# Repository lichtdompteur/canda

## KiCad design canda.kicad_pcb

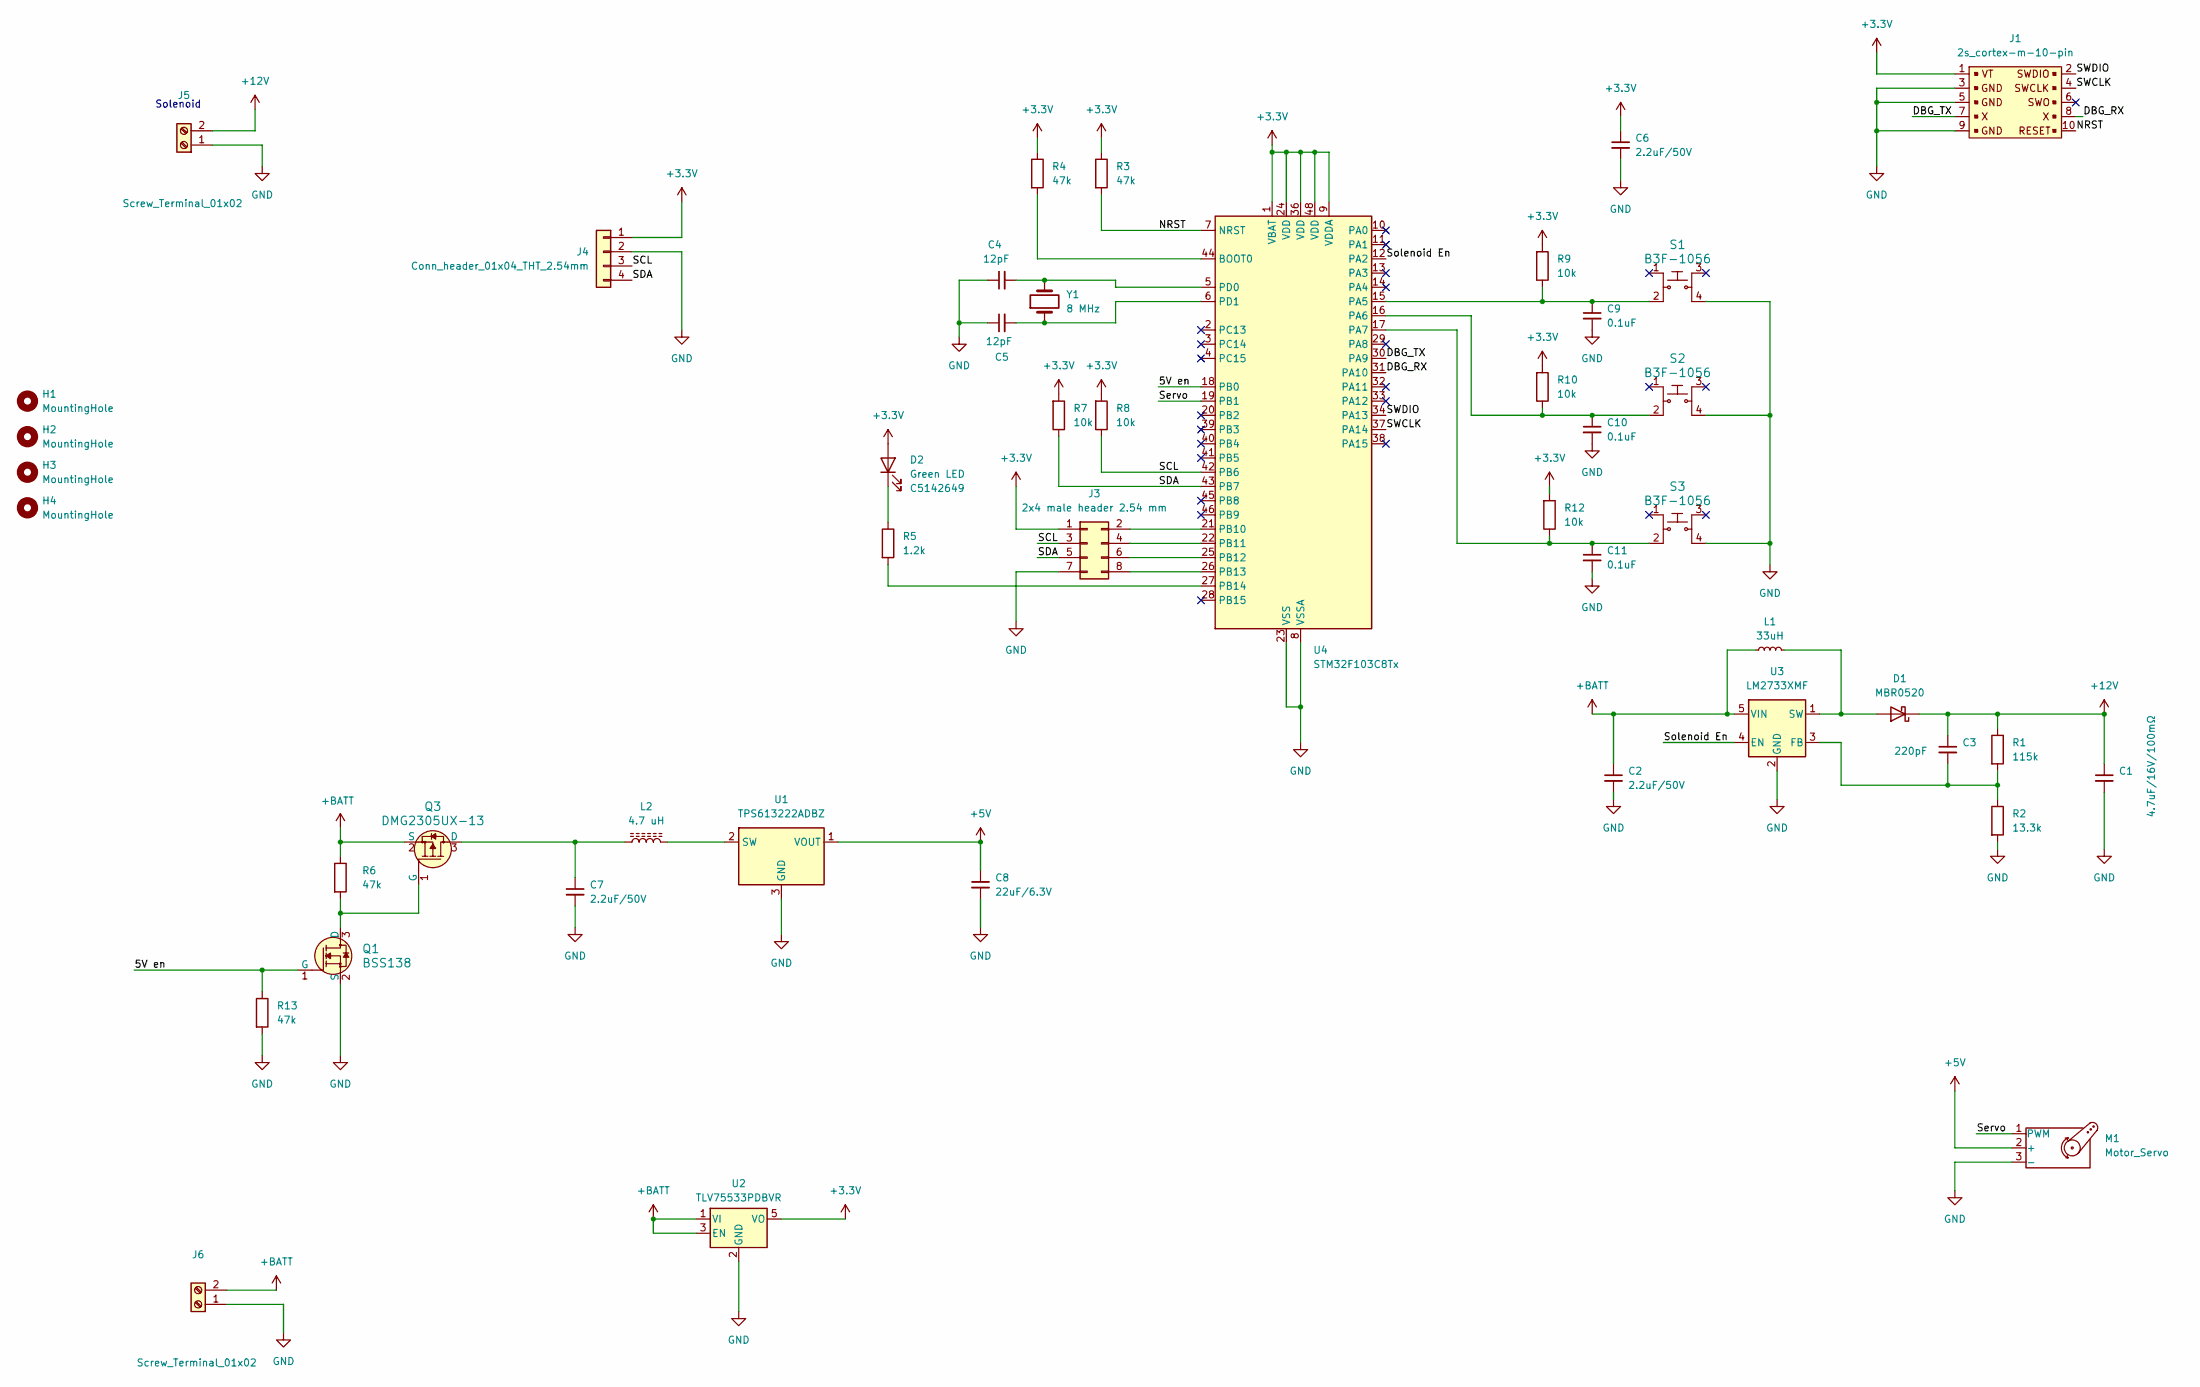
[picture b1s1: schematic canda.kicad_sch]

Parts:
C1: 4.7uF_1206_lowESR; C_1206_3216Metric; MPN EMF316AB7475KLHT; JLCPCB ID C2174986
C2, C6, C7: 2.2uF_1206_25V; C_1206_3216Metric; MPN CL31B225KBHNNNE; JLCPCB ID C12891
C3: 220pF_0603_25V; C_0603_1608Metric; MPN CC0603JRNPO9BN221; JLCPCB ID C1603
C4, C5: 12pF_0603_50V; C_0603_1608Metric; MPN C0603C120J5GACTU; JLCPCB ID C2168573
C8: 22uF_0805_6.3V; C_0805_2012Metric; MPN JMK212ABJ226MD-T; JLCPCB ID C45783
C9, C10, C11: 100nF_0603_16V; C_0603_1608Metric; MPN 0603YC104KAT2A; JLCPCB ID C14663
D1: MBR0520; D_SOD-123; MPN MBR0520-TP; Digi-Key_PN MBR0520TPMSTR-ND
D2: Green LED; LED_1206_3216Metric; MPN 150120GS75000; Digi-Key_PN 732-4990-1-ND
H1, H2, H3, H4: MountingHole; MountingHole_3.2mm_M3_ISO7380
J1: 2s_cortex-m-10-pin; PinHeader_2x5_P1.27_SMD; MPN FTSH-105-01-F-DV-K; Digi-Key_PN SAM8796-ND
J3: 2x4 male header 2.54 mm; PinHeader_2x04_P2.54mm_Vertical_SMD; MPN 54202-G0804LF; Digi-Key_PN 609-54202-G0804LF-ND
J4: Conn_header_01x04_THT_2.54mm; PinHeader_1x04_P2.54mm_Vertical; MPN 61300411121; Digi-Key_PN 732-5317-ND
J5, J6: Screw_Terminal_01x02; TerminalBlock_MaiXu_MX126-5.0-02P_1x02_P5.00mm; MPN 282836-2; Digi-Key_PN A98076-ND
L1: 33uH; L_Taiyo-Yuden_NR-60xx; MPN NR6028T330M; Digi-Key_PN 587-2631-2-ND
L2: 4.7 uH; L_Bourns-SRN6028; MPN NRS6028T4R7MMGKV; Digi-Key_PN 587-3639-2-ND
M1: Motor_Servo; PinHeader_1x03_P2.54mm_Vertical
Q1: BSS138; SOT-23-3; MPN BSS138; Digi-Key_PN BSS138CT-ND
Q3: DMG2305UX-13; SOT-23-3; MPN DMG2305UX-13; Digi-Key_PN DMG2305UX-13DICT-ND
R1: 115k_0805; R_0805_2012Metric; MPN RC0805FR-07115KL; JLCPCB ID C274364
R2: 13.3k_0805; R_0805_2012Metric; MPN RC0805FR-0713K3L; JLCPCB ID C274912
R3, R4, R6, R13: 47k_0805; R_0805_2012Metric; MPN RC0805FR-0747KL; JLCPCB ID C126351
R5: 1.2k_0805; R_0805_2012Metric; MPN RC0805FR-071K2L; JLCPCB ID C114526
R7, R8, R9, R10, R12: 10k_0805; R_0805_2012Metric; MPN CRCW080510K0FKEA; JLCPCB ID C84376
S1, S2, S3: B3F-1056; SW_TH_Tactile_Omron_B3F-1052; MPN B3F-1056; Digi-Key_PN Z4425-ND
U1: TPS613222ADBZ; SOT-23
U2: TLV75533PDBVR; SOT-23-5; MPN TLV75533PDBVR; Digi-Key_PN 296-50411-1-ND
U3: LM2733XMF; SOT-23-5; MPN LM2733XMF/NOPB; Digi-Key_PN LM2733XMF/NOPBTR-ND
U4: STM32F103C8Tx; LQFP-48_7x7mm_P0.5mm
Y1: 8 MHz; Crystal_HC49-U_Vertical; MPN ATS08A-E

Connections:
+3.3V: C6.1, D2.2 (A), J1.1, J3.1, J4.1, R3.1, R4.1, R7.1, R8.1, R9.1, R10.1, R12.1, U2.5 (VO), U4.1 (VBAT), U4.9 (VDDA), U4.24 (VDD), U4.36 (VDD), U4.48 (VDD)
+5V: C8.1, M1.2 (+), U1.1 (VOUT)
+12V: C1.1, C3.1, D1.1 (K), J5.2, R1.1
+BATT: C2.1, J6.2, L1.1, Q3.2 (S), R6.1, U2.1 (VI), U2.3 (EN), U3.5 (VIN)
/5V en: Q1.1 (G), R13.1, U4.18 (PB0)
/DBG_RX: J1.8, U4.31 (PA10)
/DBG_TX: J1.7, U4.30 (PA9)
/NRST: J1.10, R3.2, U4.7 (NRST)
/SCL: J3.3, J4.3, R8.2, U4.42 (PB6)
/SDA: J3.5, J4.4, R7.2, U4.43 (PB7)
/SWCLK: J1.4, U4.37 (PA14)
/SWDIO: J1.2, U4.34 (PA13)
/Servo: M1.1 (PWM), U4.19 (PB1)
/Solenoid En: U3.4 (EN), U4.12 (PA2)
GND: C1.2, C2.2, C4.1, C5.1, C6.2, C7.2, C8.2, C9.2, C10.2, C11.2, J1.3, J1.5, J1.9, J3.7, J4.2, J5.1, J6.1, M1.3 (-), Q1.2 (S), R2.2, R13.2, S1.4, S2.4, S3.4, U1.3 (GND), U2.2 (GND), U3.2 (GND), U4.8 (VSSA), U4.23 (VSS), U4.35 (VSS), U4.47 (VSS)
unnamed: D1.2 (A), L1.2, U3.1 (SW)
unnamed: D2.1 (K), R5.1
unnamed: J3.2, U4.21 (PB10)
unnamed: J3.4, U4.22 (PB11)
unnamed: J3.6, U4.25 (PB12)
unnamed: J3.8, U4.26 (PB13)
unnamed: Q1.3 (D), Q3.1 (G), R6.2
unnamed: C7.1, L2.1, Q3.3 (D)
unnamed: L2.2, U1.2 (SW)
unnamed: C3.2, R1.2, R2.1, U3.3 (FB)
unnamed: R4.2, U4.44 (BOOT0)
unnamed: C9.1, R9.2, S1.2, U4.15 (PA5)
unnamed: C10.1, R10.2, S2.2, U4.16 (PA6)
unnamed: C11.1, R12.2, S3.2, U4.17 (PA7)
unnamed: R5.2, U4.27 (PB14)
unnamed: C4.2, U4.5 (PD0), Y1.2
unnamed: C5.2, U4.6 (PD1), Y1.1

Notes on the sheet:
Solenoid

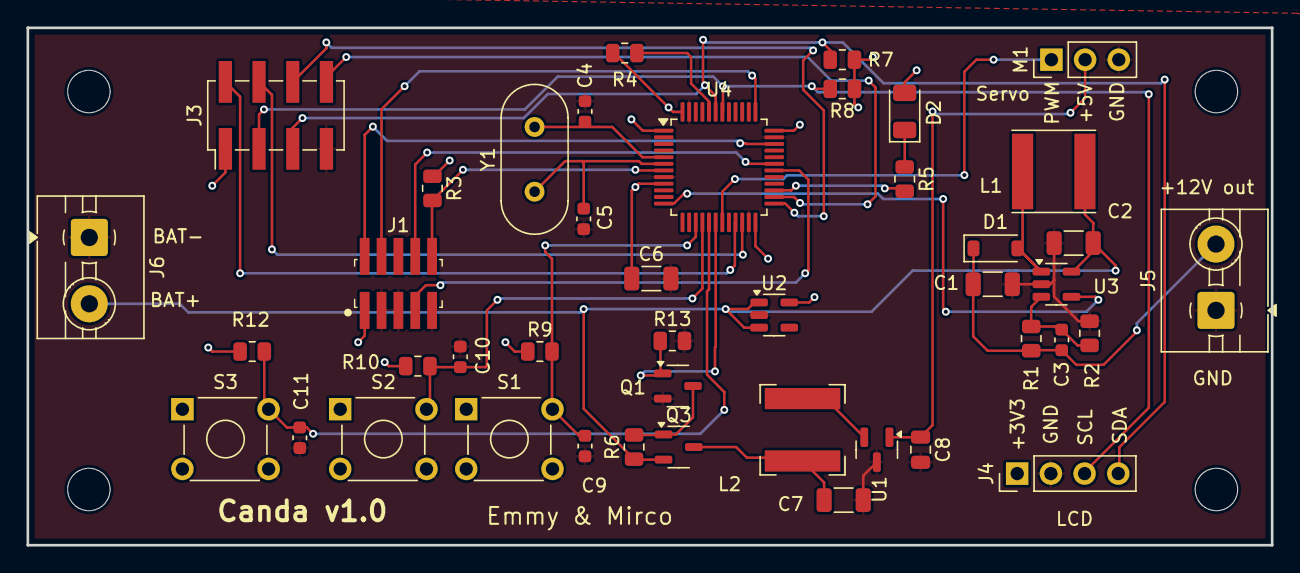
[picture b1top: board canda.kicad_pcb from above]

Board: 2 copper layers, 93.8 x 39.0 mm, 47 parts (0 on the bottom side), 32 nets.

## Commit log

2025-08-18 first version
2025-08-20 update workflow
2025-08-20 update terminal block
2025-08-20 fix file name
2025-09-20 erc and drc as separate steps
2025-09-20 Remove push action
2025-09-20 Use custom config file
2025-09-20 Fix Errors
2025-09-20 remove things
2025-09-20 rename
2025-09-20 add git version to artifacts
2025-09-20 remove verbosity
2025-10-11 add uc bom info
